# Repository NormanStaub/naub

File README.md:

# naub

An open-source USB hardware mixer for **independent application and system audio
control**. Turn a knob to set per-app or system volume; press to mute. Built on a
Raspberry Pi Pico 2 (RP2350) with rotary encoders and an e-paper display.

- **System volume** works driverless via USB HID Consumer Control (Windows /
  macOS / Linux).
- **Per-app volume** runs through a small host helper over USB CDC serial
  (Windows WASAPI · Linux PipeWire · macOS via virtual audio driver).

## Project docs

| Doc | Purpose |
|-----|---------|
| [`WRITEUP.md`](WRITEUP.md) | **Developer handoff** — current state, decisions, gotchas, roadmap |
| [`PROTOCOL.md`](PROTOCOL.md) | **Host ⇄ device CDC protocol** — proto=2 (V2 mixer, meters, EQ); proto=1 is the retired V1 |
| [`firmware/v2/STATUS.md`](firmware/v2/STATUS.md) | **V2 state** — what landed, what is unfinished |
| [`V1_BUILD.md`](V1_BUILD.md) | V1 hardware build outline |
| [`BOM_V2.md`](BOM_V2.md) | Bill of materials (V2; [`BOM.md`](BOM.md) is V1) |
| [`WIRING.md`](WIRING.md) | Pin-by-pin wiring & pinout spec |

## Software

| Dir | Purpose |
|-----|---------|
| [`firmware/v2/`](firmware/v2/) | **Current** CircuitPython firmware — 128×64 LCD, mixer + EQ + config screens |
| [`naubd/`](naubd/) | **The always-on Windows daemon** (Rust) — meters, per-app volume, EQ. Runs at login |
| [`firmware/v2/host/`](firmware/v2/host/) | V2 host-side tooling — the development bridge, deploy, asset generators |
| [`firmware/`](firmware/) | V1 firmware (e-paper) — retired |
| [`host/`](host/) | V1 Windows helper (Python) — **archived**, superseded by `naubd/` |

## Status

Hardware bring-up. **V2 is the live line**: its firmware and the `naubd` daemon
are what run day to day. V1 (e-paper panel, proto=1, the Python host in
`host/`) is retired and kept only for reference. Hardware and firmware are
intended to be open source.

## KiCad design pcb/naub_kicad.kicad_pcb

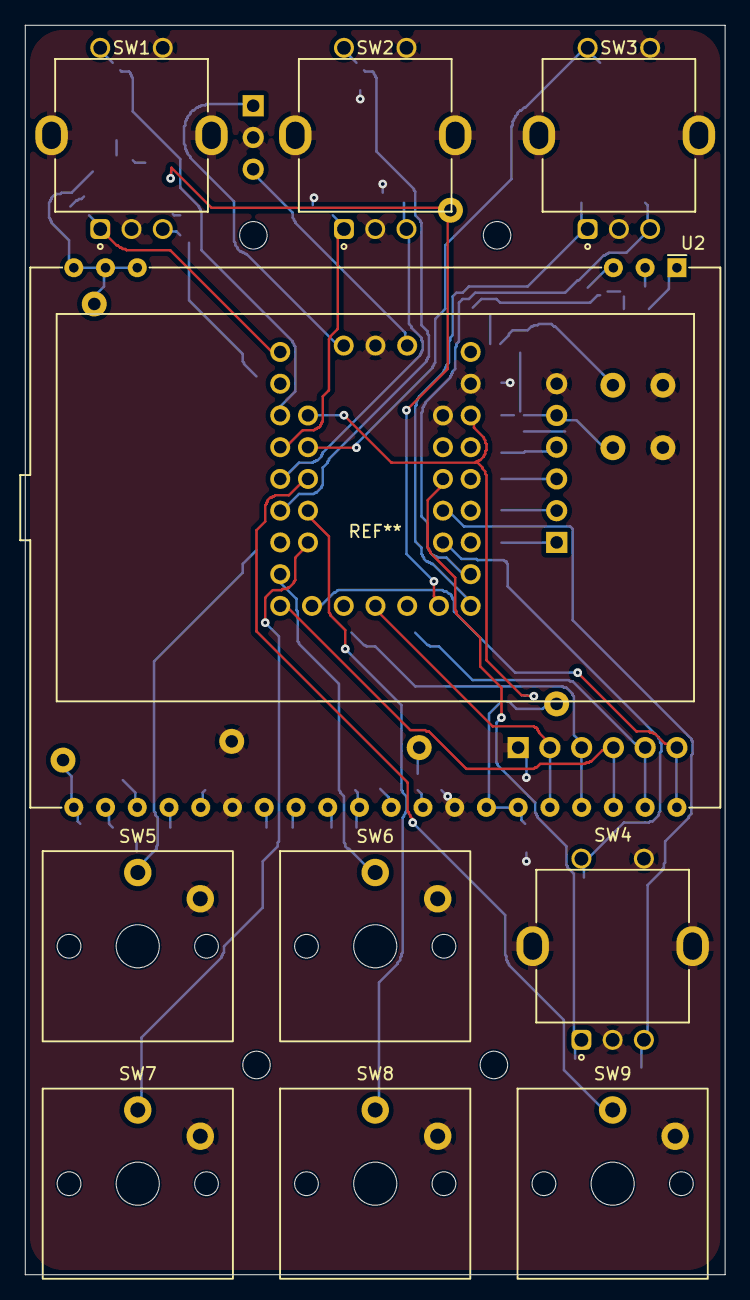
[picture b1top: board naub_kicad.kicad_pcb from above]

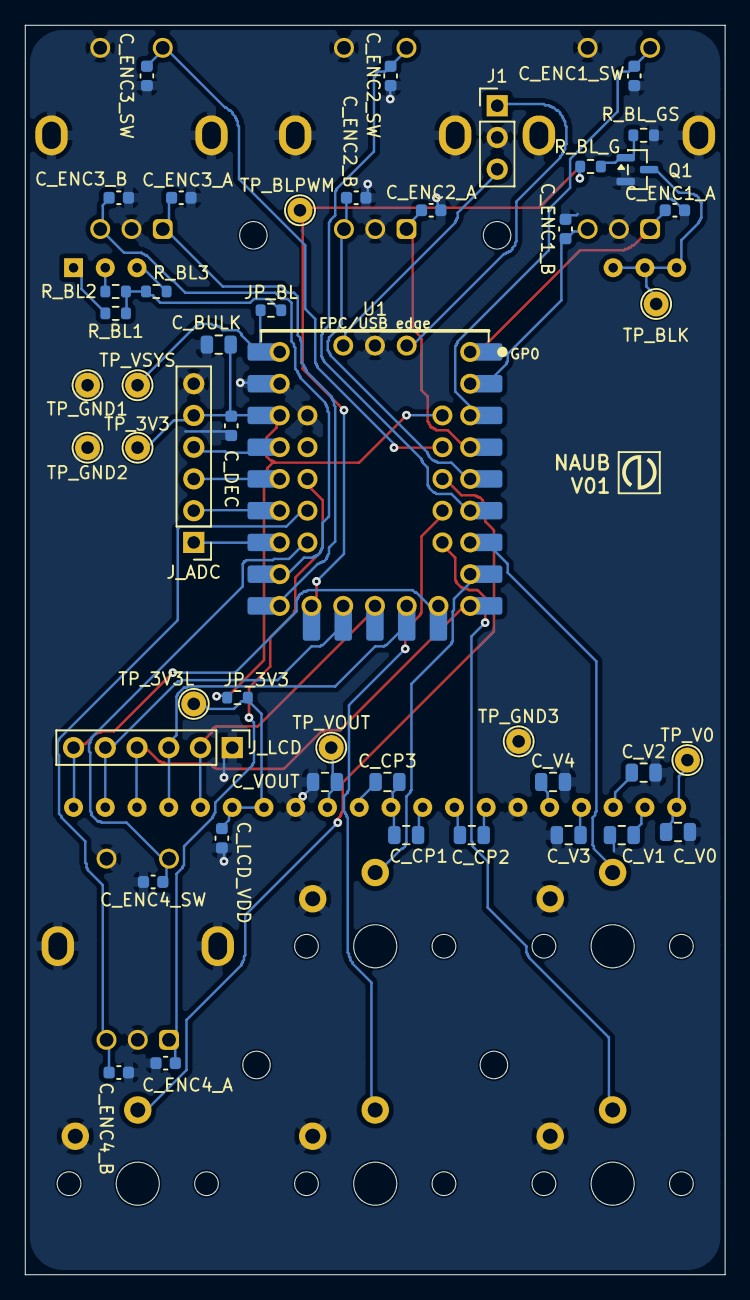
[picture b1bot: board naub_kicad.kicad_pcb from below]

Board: 2 copper layers, 56.0 x 100.0 mm, 56 parts (46 on the bottom side), 50 nets.

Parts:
C_BULK: 10uF; C_0805_2012Metric
C_CP1, C_CP2, C_CP3: 1uF; C_0805_2012Metric
C_DEC: 100nF; C_0603_1608Metric
C_ENC1_A, C_ENC1_B, C_ENC2_A, C_ENC2_B, C_ENC3_A, C_ENC3_B, C_ENC4_A, C_ENC4_B: 10nF; C_0603_1608Metric
C_ENC1_SW, C_ENC2_SW, C_ENC3_SW, C_ENC4_SW: 100nF; C_0603_1608Metric
C_LCD_VDD: 100nF; C_0603_1608Metric
C_V0, C_V1, C_V2, C_V3, C_V4: 1uF; C_0805_2012Metric
C_VOUT: 1uF; C_0805_2012Metric
J1: SWD; PinHeader_1x03_P2.54mm_Vertical
JP_3V3: 0R; R_0603_1608Metric
JP_BL: 0R; R_0603_1608Metric
J_ADC: SPARE_IO; PinHeader_1x06_P2.54mm_Vertical
J_LCD: LCD_DEBUG; PinHeader_1x06_P2.54mm_Vertical
Q1: 2N7002; SOT-23
R_BL1, R_BL2, R_BL3: 300; R_0603_1608Metric
R_BL_G: 100; R_0603_1608Metric
R_BL_GS: 10k; R_0603_1608Metric
SW1, SW2, SW3, SW4: PEC11L-4020F-S0020; RotaryEncoder_Bourns_PEC11L-4xxxF-Sxxxx_Vertical
SW5, SW6, SW7, SW8, SW9: Kailh_Choc_Red; SW_Kailh_Choc_V1
TP_3V3, TP_3V3L: TP; TestPoint_THTPad_D2.0mm_Drill1.0mm
TP_BLK: TP; TestPoint_THTPad_D2.0mm_Drill1.0mm
TP_BLPWM: TP; TestPoint_THTPad_D2.0mm_Drill1.0mm
TP_GND1, TP_GND2, TP_GND3: TP; TestPoint_THTPad_D2.0mm_Drill1.0mm
TP_V0: TP; TestPoint_THTPad_D2.0mm_Drill1.0mm
TP_VOUT: TP; TestPoint_THTPad_D2.0mm_Drill1.0mm
TP_VSYS: TP; TestPoint_THTPad_D2.0mm_Drill1.0mm
U1: Waveshare_RP2350-Tiny; Waveshare_RP2350-Tiny_Hybrid
U2: EA_DOGM128W-6; EA_DOGM128-6

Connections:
+3V3: C_BULK.1, C_DEC.1, JP_3V3.1, J_ADC.5, TP_3V3.1, U1.3V3
+3V3_LCD: C_LCD_VDD.1, JP_3V3.2, TP_3V3L.1, U2.34, U2.35
BL_A1: R_BL1.2, U2.1
BL_A2: R_BL2.2, U2.2
BL_A3: R_BL3.2, U2.3
BL_CATHODE: Q1.3, TP_BLK.1, U2.18, U2.19, U2.20
BL_PWM: R_BL_G.1, TP_BLPWM.1, U1.GP13
BL_PWM_GATE: Q1.1, R_BL_G.2, R_BL_GS.1
BTN1: SW5.1, U1.GP6
BTN2: SW6.1, U1.GP7
BTN3: SW7.1, U1.GP20
BTN4: SW8.1, U1.GP21
BTN5: SW9.1, U1.GP22
ENC1_A: C_ENC1_A.1, SW1.A, U1.GP0
ENC1_B: C_ENC1_B.1, SW1.B, U1.GP1
ENC1_SW: C_ENC1_SW.1, SW1.S1, U1.GP2
ENC2_A: C_ENC2_A.1, SW2.A, U1.GP3
ENC2_B: C_ENC2_B.1, SW2.B, U1.GP4
ENC2_SW: C_ENC2_SW.1, SW2.S1, U1.GP5
ENC3_A: C_ENC3_A.1, SW3.A, U1.GP14
ENC3_B: C_ENC3_B.1, SW3.B, U1.GP15
ENC3_SW: C_ENC3_SW.1, SW3.S1, U1.GP23
ENC4_A: C_ENC4_A.1, SW4.A, U1.GP17
ENC4_B: C_ENC4_B.1, SW4.B, U1.GP18
ENC4_SW: C_ENC4_SW.1, SW4.S1, U1.GP19
GND: C_BULK.2, C_DEC.2, C_ENC1_A.2, C_ENC1_B.2, C_ENC1_SW.2, C_ENC2_A.2, C_ENC2_B.2, C_ENC2_SW.2, C_ENC3_A.2, C_ENC3_B.2, C_ENC3_SW.2, C_ENC4_A.2, C_ENC4_B.2, C_ENC4_SW.2, C_LCD_VDD.2, C_V0.2, C_V1.2, C_V2.2, C_V3.2, C_V4.2, C_VOUT.2, J1.2, J_ADC.6, J_LCD.1, Q1.2, R_BL_GS.2, SW1.C, SW1.S2, SW1.SH, SW2.C, SW2.S2, SW2.SH, SW3.C, SW3.S2, SW3.SH, SW4.C, SW4.S2, SW4.SH, SW5.2, SW6.2, SW7.2, SW8.2, SW9.2, TP_GND1.1, TP_GND2.1, TP_GND3.1, U1.GND, U2.26, U2.33
LCD_A0: J_LCD.4, U1.GP8, U2.38
LCD_CAP1N: C_CP1.2, C_CP3.2, U2.30
LCD_CAP1P: C_CP1.1, U2.29
LCD_CAP2N: C_CP2.2, U2.27
LCD_CAP2P: C_CP2.1, U2.28
LCD_CAP3P: C_CP3.1, U2.31
LCD_CS: J_LCD.6, U1.GP9, U2.40
LCD_RST: J_LCD.5, U1.GP12, U2.39
LCD_SCL: J_LCD.3, U1.GP10, U2.37
LCD_SI: J_LCD.2, U1.GP11, U2.36
LCD_V0: C_V0.1, TP_V0.1, U2.21
LCD_V1: C_V1.1, U2.22
LCD_V2: C_V2.1, U2.23
LCD_V3: C_V3.1, U2.24
LCD_V4: C_V4.1, U2.25
LCD_VOUT: C_VOUT.1, TP_VOUT.1, U2.32
SPARE_GP26: J_ADC.1, U1.GP26
SPARE_GP27: J_ADC.2, U1.GP27
SPARE_GP28: J_ADC.3, U1.GP28
SPARE_GP29: J_ADC.4, U1.GP29
SWCLK: J1.1, U1.SWCLK
SWDIO: J1.3, U1.SWDIO
VSYS_5V: JP_BL.1, TP_VSYS.1, U1.VSYS
VSYS_BL: JP_BL.2, R_BL1.1, R_BL2.1, R_BL3.1

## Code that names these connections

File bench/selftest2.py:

# Retest the back solder-through pads via microcontroller.pin (board.* omits them)
import board, digitalio, microcontroller, time

BACK = [("GPIO17","ENC4_A"),("GPIO18","ENC4_B"),("GPIO19","ENC4_SW"),
        ("GPIO20","BTN3"),("GPIO21","BTN4"),("GPIO22","BTN5"),("GPIO23","ENC3_SW")]
OTHER = [("GPIO16","onboard WS2812"),("GPIO24","mode-select NC"),("GPIO25","mode-select NC")]

def pulltest(pin):
    d = digitalio.DigitalInOut(pin)
    try:
        d.direction = digitalio.Direction.INPUT
        d.pull = digitalio.Pull.UP;   time.sleep(0.003); hi = d.value
        d.pull = digitalio.Pull.DOWN; time.sleep(0.003); lo = d.value
        return hi, lo
    finally:
        d.deinit()

print("\n" + "="*58)
print("RETEST: back solder-through pads via microcontroller.pin")
print("="*58)
names = sorted(n for n in dir(microcontroller.pin) if n.startswith("GPIO"))
print("microcontroller.pin exposes:", len(names), "GPIO ->", ", ".join(names))
print("board.* exposes:", len([n for n in dir(board) if n.startswith("GP")]), "GP names")

fails = []
print("\n--- naub back-pad assignments ---")
for pname, fn in BACK:
    try:
        hi, lo = pulltest(getattr(microcontroller.pin, pname))
        ok = (hi is True) and (lo is False)
        print("  %-7s %-10s up=%-5s dn=%-5s  %s" % (pname, fn, hi, lo, "PASS" if ok else "FAIL"))
        if not ok: fails.append(pname)
    except Exception as e:
        print("  %-7s %-10s ERROR %s: %s" % (pname, fn, type(e).__name__, e))
        fails.append(pname)

print("\n--- other on-die pins ---")
for pname, note in OTHER:
    try:
        hi, lo = pulltest(getattr(microcontroller.pin, pname))
        print("  %-7s %-16s up=%-5s dn=%-5s" % (pname, note, hi, lo))
    except Exception as e:
        print("  %-7s %-16s %s: %s" % (pname, note, type(e).__name__, e))

print("\n--- peripherals on the back pads ---")
try:
    import rotaryio
    e4 = rotaryio.IncrementalEncoder(microcontroller.pin.GPIO17, microcontroller.pin.GPIO18)
    print("  PIO quadrature ENC4 on GPIO17/18   PASS (position=%d)" % e4.position)
    e4.deinit()
except Exception as ex:
    print("  PIO ENC4 FAIL:", ex); fails.append("ENC4-PIO")

print("\n" + "="*58)
print(("RESULT: FAIL -> " + ", ".join(fails)) if fails else "RESULT: ALL BACK PADS PASS")
print("="*58)
while True:
    time.sleep(1)

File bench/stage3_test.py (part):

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    ("ENC3", mp.GPIO14, mp.GPIO15, mp.GPIO23),   # SW remapped GP16 -> GP23
    ("ENC4", mp.GPIO17, mp.GPIO18, mp.GPIO19),
]
BUTTONS = [("BTN1", mp.GPIO6), ("BTN2", mp.GPIO7), ("BTN3", mp.GPIO20),
           ("BTN4", mp.GPIO21), ("BTN5", mp.GPIO22)]
SWITCHES = [(e[0] + "_SW", e[3]) for e in ENCODERS] + BUTTONS         # 9 switches
ALL_INPUTS = ([(n + "_A", a) for n, a, b, s in ENCODERS] +
              [(n + "_B", b) for n, a, b, s in ENCODERS] + SWITCHES)  # 17 inputs
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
